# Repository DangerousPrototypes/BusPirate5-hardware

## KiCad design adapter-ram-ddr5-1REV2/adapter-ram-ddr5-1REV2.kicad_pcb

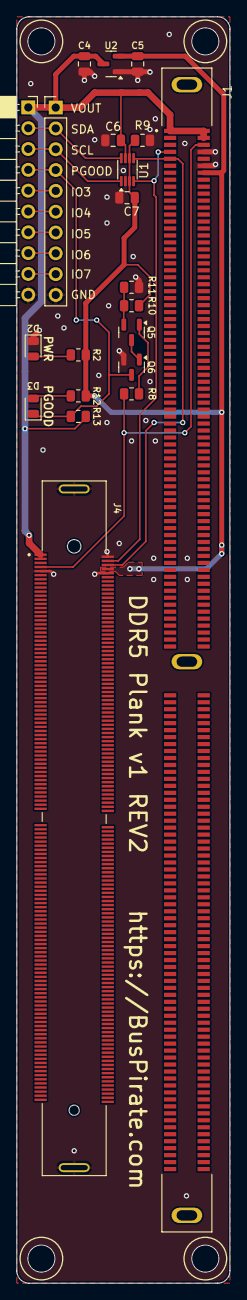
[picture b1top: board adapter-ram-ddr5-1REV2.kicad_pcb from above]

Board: 2 copper layers, 26.0 x 154.5 mm, 21 parts (0 on the bottom side), 19 nets.

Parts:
C4, C5, C6, C7: 10uF/6.3V; C_0805_2012Metric
D2, D3: LED; LED_0805_2012Metric
J1: DDR504111002KQ; DDR5 UDIMM GENERIC
J2: Conn_01x10; PinSocket_1x10_P2.54mm_Horizontal
J3: Conn_01x10; PinHeader_1x10_P2.54mm_Vertical
J4: 10160554-001SHLF; AMPHENOL_10160554-001SHLF
Q5: BC807; SOT-23
Q6: BC817; SOT-23
R2, R12, R13: 6.8K; R_0805_2012Metric
R8, R9: 1K; R_0805_2012Metric
R10: 680R; R_0805_2012Metric
R11: 330R; R_0805_2012Metric
U1: TXS0102DCU; VSSOP-8_2.3x2mm_P0.5mm
U2: ME6206A33XG; SOT-23

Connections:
+3.3V: C5.1, C7.1, J1.151, J4.8, R2.1, R9.2, R10.2, R12.1, U1.3 (VCCA), U1.6 (OE), U2.2 (VO)
BULK_VIN: C4.1, C6.2, J1.01, J1.145, J1.146, J2.1, J3.1, J4.1, J4.3, R13.2, U1.7 (VCCB), U2.3 (VI)
GND: C4.2, C5.2, C6.1, C7.2, D2.1 (K), J1.148, J1.150, J2.10, J3.10, J4.2, J4.9, J4.10, J4.SH, Q6.2 (E), R9.1, R11.1, U1.2 (GND), U2.1 (GND)
HSCL: J1.04, J4.4, U1.4 (A2)
HSDA: J1.05, J4.6, U1.5 (A1)
unnamed: D2.2 (A), R2.2
unnamed: D3.2 (A), R12.2
unnamed: J2.5, J3.5
unnamed: J2.6, J3.6
unnamed: J2.7, J3.7
unnamed: J2.8, J3.8
unnamed: J2.9, J3.9
unnamed: Q5.1 (B), R8.2
unnamed: Q5.3 (C), Q6.1 (B)
unnamed: Q5.2 (E), R10.1, R11.2
PWR_GOOD: J1.147, J4.7, R8.1
PWR_GOOD_OUT: D3.1 (K), J2.4, J3.4, Q6.3 (C), R13.1
SCL: J2.3, J3.3, U1.1 (B2)
SDA: J2.2, J3.2, U1.8 (B1)

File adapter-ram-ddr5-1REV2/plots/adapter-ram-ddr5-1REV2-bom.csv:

"Reference","Value","Footprint","Qty","szlcsc_partnum","DNP"
"C4,C5,C6,C7","10uF/6.3V","Capacitor_SMD:C_0805_2012Metric","4","C307525",""
"D2,D3","LED","LED_SMD:LED_0805_2012Metric","2","",""
"J1","DDR504111002KQ","footprints:DDR5 UDIMM GENERIC","1","",""
"J2","Conn_01x10","Connector_PinSocket_2.54mm:PinSocket_1x10_P2.54mm_Horizontal","1","",""
"J4","10160554-001SHLF","footprints:AMPHENOL_10160554-001SHLF","1","",""
"Q5","BC807","Package_TO_SOT_SMD:SOT-23","1","C21714130",""
"Q6","BC817","Package_TO_SOT_SMD:SOT-23","1","C39828",""
"R2,R12,R13","6.8K","Resistor_SMD:R_0805_2012Metric","3","C17772",""
"R8,R9","1K","Resistor_SMD:R_0805_2012Metric","2","C17513",""
"R10","680R","Resistor_SMD:R_0805_2012Metric","1","C17798",""
"R11","330R","Resistor_SMD:R_0805_2012Metric","1","C17630",""
"U1","TXS0102DCU","Package_SO:VSSOP-8_2.3x2mm_P0.5mm","1","C53434",""
"U2","ME6206A33XG","Package_TO_SOT_SMD:SOT-23","1","C161345",""

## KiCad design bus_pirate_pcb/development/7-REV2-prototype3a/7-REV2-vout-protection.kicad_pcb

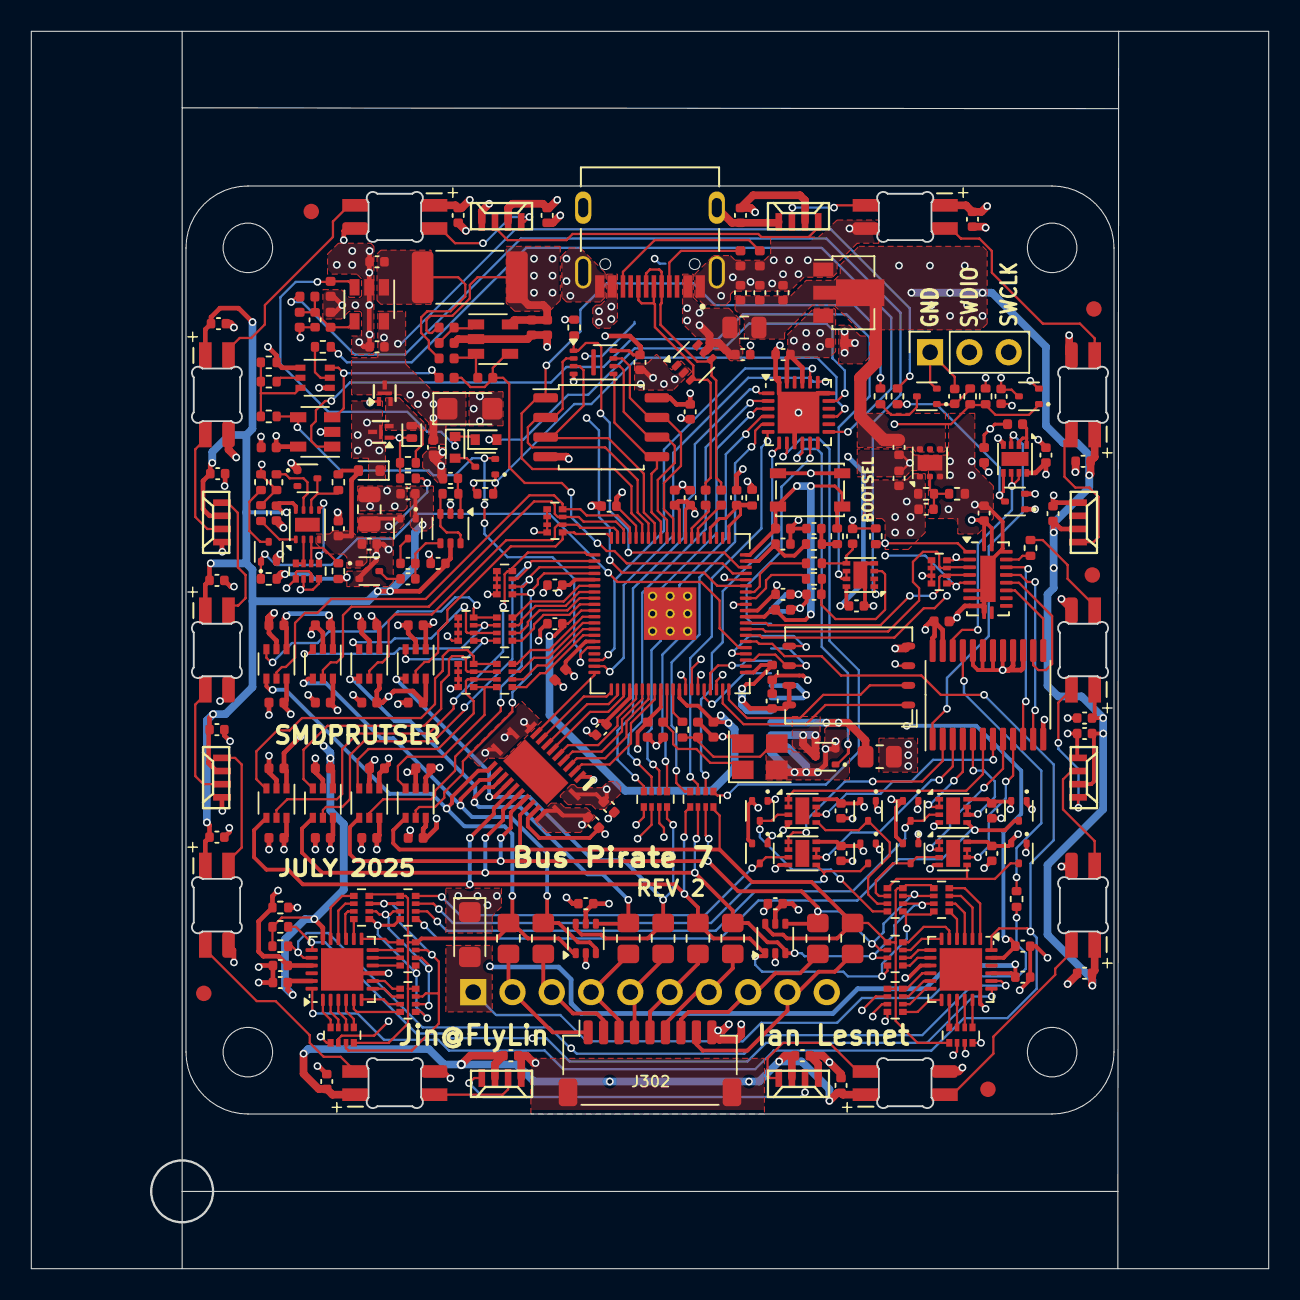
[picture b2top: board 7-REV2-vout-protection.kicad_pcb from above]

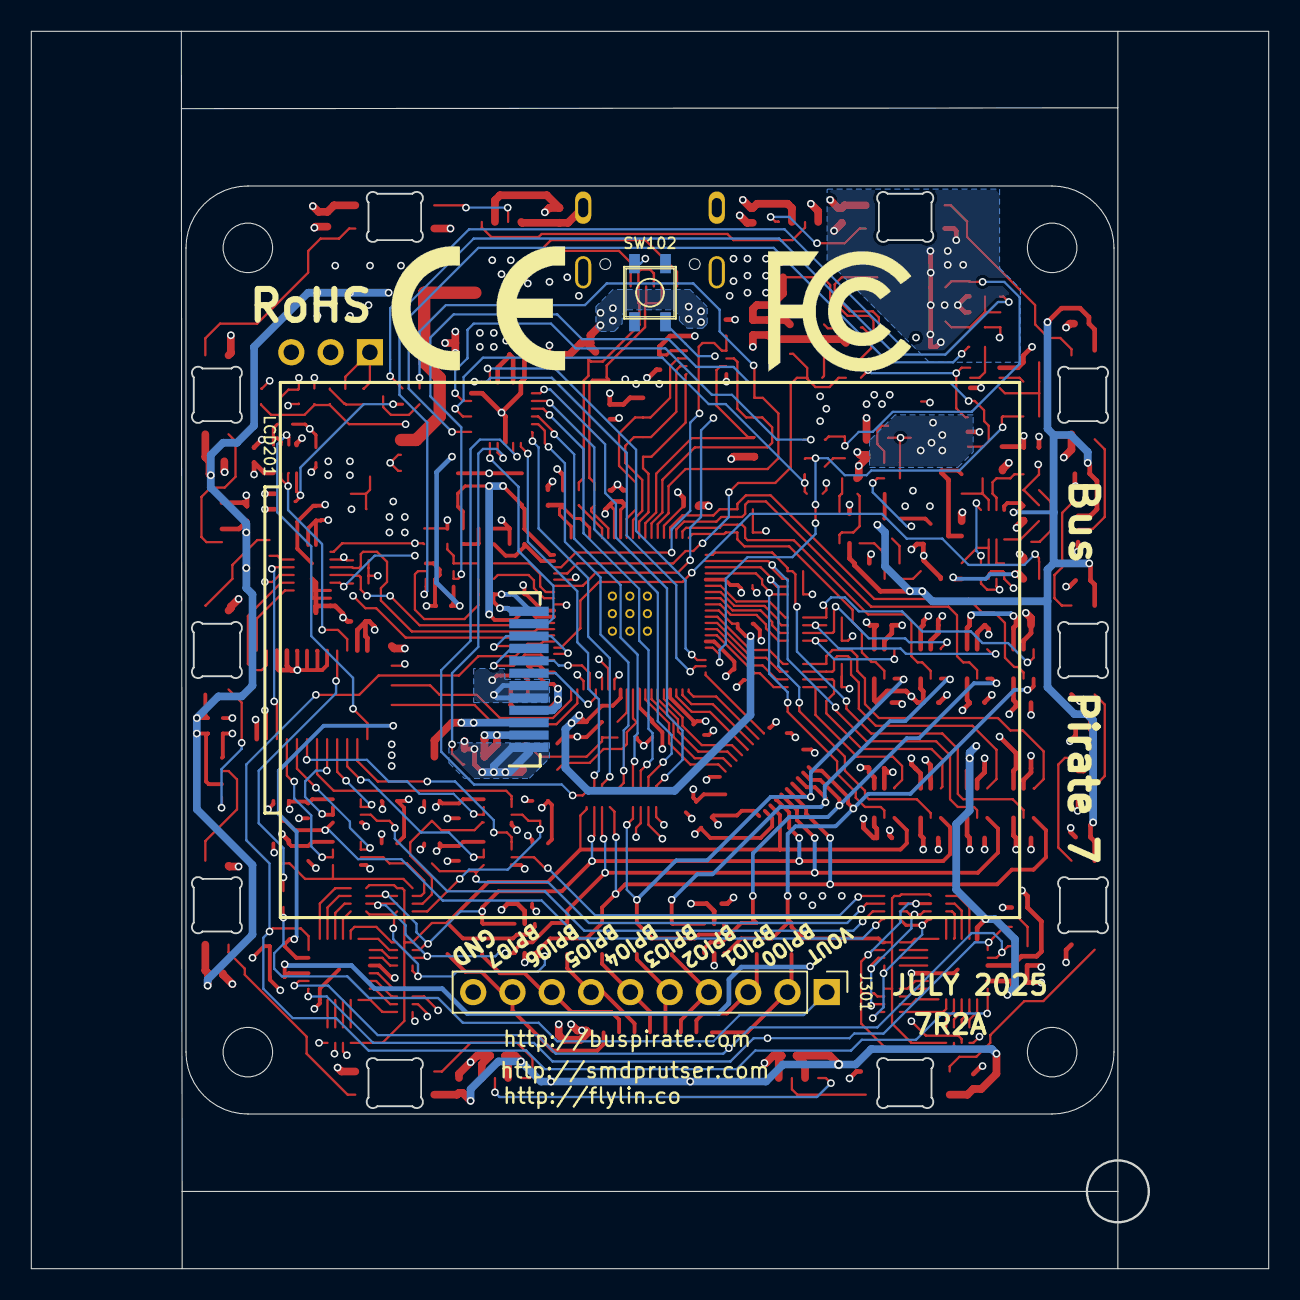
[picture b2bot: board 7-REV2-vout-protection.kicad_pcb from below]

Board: 4 copper layers, 80.0 x 80.0 mm, 276 parts (5 on the bottom side), 223 nets.

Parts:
C1, C2, C3, C5, C7, C8, C9, C14, C15, C16, C17, C20, C22, C28, C32, C110, C111, C112, C113, C114, C115, C116, C117, C118, C301, C302, C303, C304, C305, C306, C307, C308, C309, C310, C311, C312, C313, C314, C315, C316, C403, C415, C416, C503, C507, C508, C509, C510, C602, C605, C701, C702, C703, C704, C705, C706, C707, C708, C710, C712, C713, C714, C715, C716, C717, C718, C719, C720: 0.1uF; C_0402_1005Metric
C4, C6, C10, C11, C18, C19, C23, C24, C29, C36, C104, C109, C201, C202, C401, C402, C404, C407, C413, C601: 10uF/6.3V; C_0402_1005Metric
C12, C26, C408: 120pF; C_0402_1005Metric
C25, C27, C30, C31, C33, C35: 10uF/6.3v; C_0402_1005Metric
C34: 10uF/16v; C_0805_2012Metric
C105, C106: 15pF; C_0402_1005Metric
D1, D2, D3, D4, D5, D6, D7, D8, D9, D14, D15, D16: BAS40-04; SOT-523
D11: SMF24CA; D_SMF
D12: SMF5.0A; D_SMF
D13: PESD12VV1BL; D_SOD-882D
D18, D602, D603: 1N4148WT; D_SOD-523
FID1, FID2, FID3, FID4, FID5: Fiducial; Fiducial_1mm_Mask2mm
H1, H2, H3, H4: MountingHole; MountingHole_3.2mm_M3
J201: Conn_01x03; PinSocket_1x03_P2.54mm_Vertical
J202: TYPE-C-31-M-12; HRO_TYPE-C-31-M-12
J301: Conn_01x10; PinHeader_1x10_P2.54mm_Vertical
J302: Conn_01x09; JST_SH_SM09B-SRSS-TB_1x09-1MP_P1.00mm_Horizontal
L201: CBW201209U300T; L_0805_2012Metric
LCD201: TFT_20_QT200H1201
LED701, LED704, LED707, LED708, LED712, LED716, LED717, LED720: SK6812-side-a_b
LED702, LED703, LED705, LED706, LED710, LED713, LED714, LED715, LED718, LED719: SK6812-mini-e; SK6812-MINI-E
Q1, Q2, Q5, Q6: 2N7002KT; SOT-523
Q3, Q4: PMXB56EN; DFN1010D-3_SOT1215_NEX
Q601: MMDT3906DW; SOT-363_SC-70-6
Q602: BC2301T 2.8A; SOT-523
R1: 10R; R_0402_1005Metric
R2, R12, R502, R602, R603: 1k; R_0402_1005Metric
R3: 110k; R_0402_1005Metric
R4, R5, R42, R319, R401: 100k; R_0402_1005Metric
R6, R8, R9, R11, R40, R301, R406, R407, R414, R415, R606, R609, R610, R611, R613: 10k; R_0402_1005Metric
R10: 470k; R_0402_1005Metric
R13, R14, R15, R16, R17, R18, R19, R20: 120R 0.5W; R_0805_2012Metric_Pad1.20x1.40mm_HandSolder
R21, R103, R202, R203: 27R; R_0402_1005Metric
R22: 100R; R_0402_1005Metric
R23: 3.3k; R_0402_1005Metric
R33, R37: 18k; R_0402_1005Metric
R39: 180k; R_0402_1005Metric
R41, R43, R201, R204: 5.1k; R_0402_1005Metric
R209: 33R; R_0805_2012Metric
R320: 0R; R_0402_1005Metric
R403: 102k; R_0402_1005Metric
R404: 133k; R_0402_1005Metric
R405, R604, R605: 33k; R_0402_1005Metric
R601: 0R2; R_2512_6332Metric_Pad1.40x3.35mm_HandSolder
R608: 200R; R_0402_1005Metric
RN1, RN2, RN8, RN12, RN303, RN308, RN317, RN318: 100k; R_Array_Convex_4x0402
RN3, RN9: 10k; R_Array_Convex_4x0402
RN4, RN7, RN302, RN307: 4.7k; R_Array_Convex_4x0402
RN5, RN6: 2.2k; R_Array_Convex_4x0402
RN10, RN11: 1M; R_Array_Convex_4x0402
RN301, RN306: 120R; R_Array_Convex_4x0402
SW101: TS3425BA 098 2.5H 250gf; SW_SPST_PTS810
SW102: TS3315A 250gf 025; GT-TC026X-HXXX-LX
U1: RP2350B; qfn80
U2: AiP74LVC8T245QE24.TR; NXP-DHVQFN24
U4: XL9555QF24; QFN-24-1EP_4x4mm_P0.5mm_EP2.7x2.7mm
U5, U9, U10, U11, U12, U13: GS358-FR; DFN-8-1EP_2x2mm_P0.5mm_EP1.05x1.75mm
U6, U7: TCA6416ARTWR; QFN-24-1EP_4x4mm_P0.5mm_EP2.75x2.75mm
U8: APS6404L-3SQR-ZR; USON-8-3x2mm_P0.5mm_EPthin
U14, U15, U16: SP3002-04JTG; SOT-363_SC-70-6
U17: TLV75801PDRV; WSON-6-1EP_2x2mm_P0.65mm_EP1x1.6mm
U18: 74LVC2G14; SOT-363_SC-70-6
U102: W25Q128JVSIQ; SOP-8_5.28x5.23mm_P1.27mm
U105: MT29F2G01ABAGDWB-IT:G; U-PDFN-8
U117: LM393BIDSGR; WSON-8-1EP_2x2mm_P0.5mm_EP0.9x1.6mm
U301, U302, U303, U304, U305, U306, U307, U308: AiP74LVC1T45GC363.TR; SOT-363_SC-70-6
U401: ME6211A33PG-N; SOT-89-3
U402: CD4067; TSSOP-24_4.4x7.8mm_P0.65mm
U403: AP2127K-ADJ; SOT-23-5
U503: 74HCT245BQ; DHVQFN-20-1EP_2.5x4.5mm_P0.5mm_EP1x3mm
U601: GS321A-TR; SOT-23-5
U602: GSV331-TR; SOT-23-5
Y101: ABM8-272-T3; Crystal_SMD_3225-4Pin_3.2x2.5mm
logo1: fcc_logo; logo_fcc
logo2: ce_logo; CE-Logo_11.2x8mm_SilkScreen

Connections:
+1V1: C2.1, C11.1, C12.1, C117.1, C118.1, R3.1, U1.10 (DVDD), U1.32 (DVDD), U1.51 (DVDD), U17.1 (OUT)
+3V3: C1.1, C3.2, C5.2, C7.1, C8.1, C15.2, C17.2, C18.1, C19.1, C104.1, C110.1, C111.1, C112.1, C113.1, C114.1, C115.1, C116.1, C301.2, C302.2, C303.2, C307.2, C308.2, C309.2, C313.2, C314.2, C402.1, C413.1, C605.1, LCD201.4 (VCC), Q601.1 (E1), Q601.4 (E2), R1.1, R6.1, R8.1, R9.1, R21.2, R37.1, R43.1, R609.1, R613.1, SW101.1 (A), U1.5 (IOVDD), U1.15 (IOVDD), U1.24 (IOVDD), U1.29 (IOVDD), U1.41 (IOVDD), U1.50 (IOVDD), U1.60 (IOVDD), U1.68 (USB_OTP_VDD), U1.69 (QSPI_IOVDD), U1.76 (IOVDD), U2.1 (VCCA), U4.21 (VCC), U4.23 (ADDR1), U5.8 (V+), U6.23 (VCCI), U7.18 (ADDR), U7.23 (VCCI), U8.8 (VCC), U102.8 (VCC), U105.3 (WP/IO2), U105.7 (HOLD/IO3), U105.8 (VCC), U301.1 (VCCA), U302.1 (VCCA), U303.1 (VCCA), U304.1 (VCCA), U305.1 (VCCA), U306.1 (VCCA), U307.1 (VCCA), U308.1 (VCCA), U401.3 (VOUT), U602.5 (V+)
+9V: C34.1, D14.2, R33.1
+VUSB: C10.1, C20.2, C23.1, C27.1, C29.1, C30.1, C31.2, C201.2, C202.2, C401.1, C403.2, C503.2, C507.2, C508.2, C509.2, C510.2, C601.1, C602.2, C701.2, C702.2, C703.2, C704.2, C705.2, C706.2, C707.2, C708.2, C710.2, C712.2, C713.2, C714.2, C715.2, C716.2, C717.2, C718.2, C719.2, C720.2, D1.2, D2.2, D3.2, D4.2, D5.2, D6.2, D7.2, D8.2, D9.2, D14.1, L201.1, LED701.3 (VDD), LED702.1 (VDD), LED703.1 (VDD), LED704.3 (VDD), LED705.1 (VDD), LED706.1 (VDD), LED707.3 (VDD), LED708.3 (VDD), LED710.1 (VDD), LED712.3 (VDD), LED713.1 (VDD), LED714.1 (VDD), LED715.1 (VDD), LED716.3 (VDD), LED717.3 (VDD), LED718.1 (VDD), LED719.1 (VDD), LED720.3 (VDD), R209.1, R601.1, R602.2, U9.8 (V+), U10.8 (V+), U11.8 (V+), U12.8 (V+), U13.8 (V+), U14.5 (VP), U15.5 (VP), U17.4 (EN), U17.6 (IN), U18.5 (VCC), U117.8 (V+), U401.2 (VIN), U402.23 (I8), U402.24 (VCC), U503.1 (A->B), U503.20 (VCC), U601.5 (V+)
+VUSB_RAW: C24.1, J202.A4B9 (VBUS), J202.B4A9 (VBUS), L201.2, U16.5 (VP)
-5V: C33.1, C35.2, D16.1, D18.2 (A), R40.2, U117.4 (V-)
AMUX_OUT: R406.2, R407.2, U1.56 (GPIO45_ADC5)
AMUX_S0: U402.10 (S0), U503.17 (B1)
AMUX_S0_3V3: RN1.8 (R1.8), U1.47 (GPIO38), U503.3 (A1)
AMUX_S1: U402.11 (S1), U503.16 (B2)
AMUX_S1_3V3: RN1.7 (R1.8), U1.48 (GPIO39), U503.4 (A2)
AMUX_S2: U402.14 (S2), U503.15 (B3)
AMUX_S2_3V3: RN1.6 (R1.8), U1.49 (GPIO40_ADC0), U503.5 (A3)
AMUX_S3: U402.13 (S3), U503.14 (B4)
AMUX_S3_3V3: RN1.5 (R1.8), U1.52 (GPIO41_ADC1), U503.6 (A4)
BPIO0_TVS: R13.1, RN6.4 (R1.1), RN7.4 (R1.1), RN8.8 (R1.8), RN9.8 (R1.8), RN10.1 (R1.1), RN318.5 (R1.8), U2.14 (B8), U14.1 (I/O_1), U301.4 (B)
BPIO1_TVS: R14.1, RN6.3 (R1.1), RN7.3 (R1.1), RN8.7 (R1.8), RN9.7 (R1.8), RN10.2 (R1.1), RN318.6 (R1.8), U2.15 (B7), U14.3 (I/O_2), U302.4 (B)
BPIO2_TVS: R15.1, RN6.2 (R1.1), RN7.2 (R1.1), RN8.6 (R1.8), RN9.6 (R1.8), RN10.3 (R1.1), RN318.7 (R1.8), U2.16 (B6), U14.4 (I/O_3), U303.4 (B)
BPIO3_TVS: R16.1, RN6.1 (R1.1), RN7.1 (R1.1), RN8.5 (R1.8), RN9.5 (R1.8), RN10.4 (R1.1), RN318.8 (R1.8), U2.17 (B5), U14.6 (I/O_4), U304.4 (B)
BPIO4_TVS: R17.1, RN2.8 (R1.8), RN3.8 (R1.8), RN4.4 (R1.1), RN5.4 (R1.1), RN11.1 (R1.1), RN317.5 (R1.8), U2.18 (B4), U15.1 (I/O_1), U305.4 (B)
BPIO5_TVS: R18.1, RN2.7 (R1.8), RN3.7 (R1.8), RN4.3 (R1.1), RN5.3 (R1.1), RN11.2 (R1.1), RN317.6 (R1.8), U2.19 (B3), U15.3 (I/O_2), U306.4 (B)
BPIO6_TVS: R19.1, RN2.6 (R1.8), RN3.6 (R1.8), RN4.2 (R1.1), RN5.2 (R1.1), RN11.3 (R1.1), RN317.7 (R1.8), U2.20 (B2), U15.4 (I/O_3), U307.4 (B)
BPIO7_TVS: R20.1, RN2.5 (R1.8), RN3.5 (R1.8), RN4.1 (R1.1), RN5.1 (R1.1), RN11.4 (R1.1), RN317.8 (R1.8), U2.21 (B1), U15.6 (I/O_4), U308.4 (B)
BUFDIR0: RN303.8 (R1.8), U1.77 (GPIO0), U301.5 (DIR)
BUFDIR1: RN303.7 (R1.8), U1.78 (GPIO1), U302.5 (DIR)
BUFDIR2: RN303.6 (R1.8), U1.79 (GPIO2), U303.5 (DIR)
BUFDIR3: RN303.5 (R1.8), U1.80 (GPIO3), U304.5 (DIR)
BUFDIR4: RN308.8 (R1.8), U1.1 (GPIO4), U305.5 (DIR)
BUFDIR5: RN308.7 (R1.8), U1.2 (GPIO5), U306.5 (DIR)
BUFDIR6: RN308.6 (R1.8), U1.3 (GPIO6), U307.5 (DIR)
BUFDIR7: RN308.5 (R1.8), U1.4 (GPIO7), U308.5 (DIR)
BUFIO0: RN301.8 (R1.8), U1.6 (GPIO8)
BUFIO1: RN301.7 (R1.8), U1.7 (GPIO9)
BUFIO2: RN301.6 (R1.8), U1.8 (GPIO10)
BUFIO3: RN301.5 (R1.8), U1.9 (GPIO11)
BUFIO4: RN306.8 (R1.8), U1.11 (GPIO12)
BUFIO5: RN306.7 (R1.8), U1.12 (GPIO13)
BUFIO6: RN306.6 (R1.8), U1.13 (GPIO14)
BUFIO7: RN306.5 (R1.8), U1.14 (GPIO15)
BUTTONS: SW102.3, U1.55 (GPIO44_ADC4)
CURRENT_ADJ: U5.6 (-), U5.7, U602.1 (+)
CURRENT_ADJ_MCU: R415.2, U1.54 (GPIO43_ADC3)
CURRENT_DETECT: Q602.2 (S), R610.2, U1.16 (GPIO16), U602.4
CURRENT_EN: Q602.1 (G), R613.2, U4.15
CURRENT_EN_OVERRIDE: D603.2 (A), U4.17
CURRENT_RESET: R611.1, U4.13
CURRENT_SENSE: R605.1, R606.2, U1.57 (GPIO46_ADC6), U601.4
DISPLAY_BACKLIGHT: Q2.1 (G), U4.10
DISPLAY_CS: LCD201.8 (CS), U1.37 (GPIO29)
DISPLAY_DP: LCD201.7 (WR/SPI_A0), U1.36 (GPIO28)
DISPLAY_RESET: LCD201.11 (RESET), U4.11
FLASH_CS: U1.39 (GPIO31), U105.1 (CS)
GND: C1.2, C2.2, C3.1, C4.2, C5.1, C6.2, C7.2, C8.2, C9.2, C10.2, C11.2, C14.1, C15.1, C16.1, C17.1, C18.2, C19.2, C20.1, C22.2, C23.2, C24.2, C25.1, C26.2, C27.2, C29.2, C30.2, C31.1, C33.2, C34.2, C35.1, C36.2, C104.2, C105.2, C106.2, C109.2, C110.2, C111.2, C112.2, C113.2, C114.2, C115.2, C116.2, C117.2, C118.2, C201.1, C202.1, C301.1, C302.1, C303.1, C304.2, C305.2, C306.2, C307.1, C308.1, C309.1, C310.2, C311.2, C312.2, C313.1, C314.1, C315.2, C316.2, C401.2, C402.2, C403.1, C404.2, C407.2, C413.2, C415.1, C416.1, C503.1, C507.1, C508.1, C509.1, C510.1, C601.2, C602.1, C605.2, C701.1, C702.1, C703.1, C704.1, C705.1, C706.1, C707.1, C708.1, C710.1, C712.1, C713.1, C714.1, C715.1, C716.1, C717.1, C718.1, C719.1, C720.1, D1.1, D2.1, D3.1, D4.1, D5.1, D6.1, D7.1, D8.1, D9.1, D11.1 (A1), D12.2 (A2), D15.1, D16.2, J201.1, J202.A1B12 (GND), J202.B1A12 (GND), J202.S1 (SHIELD), J202.S2 (SHIELD), J202.S3 (SHIELD), J202.S4 (SHIELD), J301.10, J302.9, LCD201.1 (GND), LCD201.5 (GND), LCD201.6 (GND), LCD201.12 (GND), LED701.1 (VSS), LED702.3 (VSS), LED703.3 (VSS), LED704.1 (VSS), LED705.3 (VSS), LED706.3 (VSS), LED707.1 (VSS), LED708.1 (VSS), LED710.3 (VSS), LED712.1 (VSS), LED713.3 (VSS), LED714.3 (VSS), LED715.3 (VSS), LED716.1 (VSS), LED717.1 (VSS), LED718.3 (VSS), LED719.3 (VSS), LED720.1 (VSS), Q1.2 (S), Q2.2 (S), Q5.2 (S), Q6.2 (S), R4.1, R5.2, R11.2, R201.1, R204.1, R301.2, R401.2, R405.2, R407.1, R604.1, RN1.1 (R1.1), RN1.2 (R1.1), RN1.3 (R1.1), RN1.4 (R1.1), RN12.1 (R1.1), RN12.3 (R1.1), RN302.1 (R1.1), RN302.2 (R1.1), RN302.3 (R1.1), RN302.4 (R1.1), RN303.1 (R1.1), RN303.2 (R1.1), RN303.3 (R1.1), RN303.4 (R1.1), RN307.1 (R1.1), RN307.2 (R1.1), RN307.3 (R1.1), RN307.4 (R1.1), RN308.1 (R1.1), RN308.2 (R1.1), RN308.3 (R1.1), RN308.4 (R1.1), SW102.2, U1.81 (GND), U2.2 (DIR), U2.11 (GND), U2.12 (GND), U2.13 (GND), U2.22 (~OE), U4.9 (GND), U4.18 (ADDR0), U4.24 (ADDR2), U4.25 (EP), U5.4 (V-), U5.9 (PAD), U6.9 (GND), U6.18 (ADDR), U6.25 (EP), U7.9 (GND), U7.25 (EP), U8.4 (VSS), U9.4 (V-), U10.4 (V-), U11.4 (V-), U12.4 (V-), U13.4 (V-), U14.2 (GND), U15.2 (GND), U16.2 (GND), U17.3 (GND), U17.7 (GND), U18.2 (GND), U102.4 (VSS), U105.4 (VSS), U301.2 (GND), U302.2 (GND), U303.2 (GND), U304.2 (GND), U305.2 (GND), U306.2 (GND), U307.2 (GND), U308.2 (GND), U401.1 (GND), U402.12 (GND), U402.15 (~E), U402.16 (I15), U402.17 (I14), U402.18 (I13), U402.19 (I12), U402.20 (I11), U403.2 (GND), U503.7 (A5), U503.8 (A6), U503.9 (A7), U503.10 (GND), U503.19 (CE), U503.21 (EP), U601.2 (V-), U602.2 (V-), Y101.2, Y101.4
I2C_RESET: U1.46 (GPIO37), U6.24 (~RESET), U7.24 (~RESET)
I2C_SCL: R9.2, U1.19 (GPIO19), U4.19 (SCL), U6.19 (SCL), U7.19 (SCL)
I2C_SDA: R8.2, U1.18 (GPIO18), U4.20 (SDA), U6.20 (SDA), U7.20 (SDA)
LA_BPIO0_TVS: U1.20 (GPIO20), U2.10 (A8)
LA_BPIO1_TVS: U1.21 (GPIO21), U2.9 (A7)
LA_BPIO2_TVS: U1.22 (GPIO22), U2.8 (A6)
LA_BPIO3_TVS: U1.23 (GPIO23), U2.7 (A5)
LA_BPIO4_TVS: U1.25 (GPIO24), U2.6 (A4)
LA_BPIO5_TVS: U1.26 (GPIO25), U2.5 (A3)
LA_BPIO6_TVS: U1.27 (GPIO26), U2.4 (A2)
LA_BPIO7_TVS: U1.28 (GPIO27), U2.3 (A1)
LEDS_CDO: R502.1, U503.18 (B0)
MCU_BOOTLOAD: R12.2, U1.75 (QSPI_SS), U102.1 (CS)
MCU_RESET: C22.1, Q5.3 (D), U1.35 (RUN)
MUX_BPIO0_TVS: U9.1, U9.2 (-), U402.2 (I7)
MUX_BPIO1_TVS: U9.6 (-), U9.7, U402.3 (I6)
MUX_BPIO2_TVS: U10.1, U10.2 (-), U402.4 (I5)
MUX_BPIO3_TVS: U10.6 (-), U10.7, U402.5 (I4)
MUX_BPIO4_TVS: U11.1, U11.2 (-), U402.6 (I3)
MUX_BPIO5_TVS: U11.6 (-), U11.7, U402.7 (I2)
MUX_BPIO6_TVS: U12.1, U12.2 (-), U402.8 (I1)
MUX_BPIO7_TVS: U12.6 (-), U12.7, U402.9 (I0)
MUX_VREF_VOUT: U13.6 (-), U13.7, U402.22 (I9)
unnamed: C6.1, R21.1, R103.2
unnamed: C26.1, R39.1, U18.1
unnamed: C28.1, C32.1, U18.4
unnamed: C28.2, D14.3
unnamed: C32.2, D16.3
unnamed: C106.1, R2.1, Y101.3
unnamed: D13.1 (A1), Q3.1 (G), Q4.1 (G), R22.1, R23.1, R33.2, R41.1, R42.2
unnamed: D13.2 (A2), Q3.2 (S), Q4.2 (S), R42.1
unnamed: D602.2 (A), Q602.3 (D)
unnamed: J202.A5 (CC1), R201.2
unnamed: J202.B5 (CC2), R204.2
unnamed: J301.2, J302.1, R13.2
unnamed: J301.3, J302.2, R14.2
unnamed: J301.4, J302.3, R15.2
unnamed: J301.5, J302.4, R16.2
unnamed: J301.6, J302.5, R17.2
unnamed: J301.7, J302.6, R18.2
unnamed: J301.8, J302.7, R19.2
unnamed: J301.9, J302.8, R20.2
unnamed: LCD201.3 (LED-A), R209.2
unnamed: LCD201.2 (LED-K), Q2.3 (D)
unnamed: LED701.4 (DI), LED702.2 (DO)
unnamed: LED701.2 (DO), LED704.4 (DI)
unnamed: LED702.4 (DI), LED706.2 (DO)
unnamed: LED703.4 (DI), LED704.2 (DO)
unnamed: LED703.2 (DO), LED705.4 (DI)
unnamed: LED705.2 (DO), LED720.4 (DI)
unnamed: LED706.4 (DI), LED708.2 (DO)
unnamed: LED707.4 (DI), LED719.2 (DO)
unnamed: LED707.2 (DO), LED713.4 (DI)
unnamed: LED708.4 (DI), LED710.2 (DO)
unnamed: LED710.4 (DI), LED712.2 (DO)
unnamed: LED712.4 (DI), LED714.2 (DO)
unnamed: LED713.2 (DO), LED715.4 (DI)
unnamed: LED714.4 (DI), LED718.2 (DO)
unnamed: LED715.2 (DO), LED716.4 (DI)
unnamed: LED716.2 (DO), LED717.4 (DI)
unnamed: LED717.2 (DO), LED718.4 (DI)
unnamed: LED719.4 (DI), R502.2
unnamed: Q1.3 (D), R12.1
unnamed: C36.1, Q1.1 (G), R10.2
unnamed: Q5.1 (G), R10.1, R11.1, SW101.2 (B)
unnamed: Q6.3 (D), R23.2
unnamed: Q601.2 (B1), R611.2
unnamed: Q601.6 (C1), R608.2, R609.2, R610.1
unnamed: Q601.5 (B2), R608.1
unnamed: Q601.3 (C2), R606.1, U602.3 (-)
unnamed: R22.2, U117.7
unnamed: R39.2, U18.3, U18.6
unnamed: R41.2, U117.1
unnamed: RN2.1 (R1.1), U6.13
unnamed: RN2.2 (R1.1), U6.12
unnamed: RN2.3 (R1.1), U6.11
unnamed: RN2.4 (R1.1), U6.10
unnamed: RN3.1 (R1.1), U6.17
unnamed: RN3.2 (R1.1), U6.16
unnamed: RN3.3 (R1.1), U6.15
unnamed: RN3.4 (R1.1), U6.14
unnamed: RN4.8 (R1.8), U6.5 (P04)
unnamed: RN4.7 (R1.8), U6.6 (P05)
unnamed: RN4.6 (R1.8), U6.7 (P06)
unnamed: RN4.5 (R1.8), U6.8 (P07)
unnamed: RN5.8 (R1.8), U6.1 (P00)
unnamed: RN5.7 (R1.8), U6.2 (P01)
unnamed: RN5.6 (R1.8), U6.3 (P02)
unnamed: RN5.5 (R1.8), U6.4 (P03)
unnamed: RN6.8 (R1.8), U7.1 (P00)
unnamed: RN6.7 (R1.8), U7.2 (P01)
unnamed: RN6.6 (R1.8), U7.3 (P02)
unnamed: RN6.5 (R1.8), U7.4 (P03)
unnamed: RN7.8 (R1.8), U7.5 (P04)
unnamed: RN7.7 (R1.8), U7.6 (P05)
unnamed: RN7.6 (R1.8), U7.7 (P06)
unnamed: RN7.5 (R1.8), U7.8 (P07)
unnamed: RN8.1 (R1.1), U7.13
unnamed: RN8.2 (R1.1), U7.12
unnamed: RN8.3 (R1.1), U7.11
unnamed: RN8.4 (R1.1), U7.10
unnamed: RN9.1 (R1.1), U7.17
unnamed: RN9.2 (R1.1), U7.16
unnamed: RN9.3 (R1.1), U7.15
unnamed: RN9.4 (R1.1), U7.14
unnamed: RN10.8 (R1.8), U4.1 (P00)
unnamed: RN10.7 (R1.8), U4.2 (P01)
unnamed: RN10.6 (R1.8), U4.3 (P02)
unnamed: RN10.5 (R1.8), U4.4 (P03)
unnamed: RN11.8 (R1.8), U4.5 (P04)
unnamed: RN11.7 (R1.8), U4.6 (P05)
unnamed: RN11.6 (R1.8), U4.7 (P06)
unnamed: RN11.5 (R1.8), U4.8 (P07)
unnamed: RN12.7 (R1.8), RN12.8 (R1.8), U117.2 (-)
unnamed: R37.2, RN12.6 (R1.8), U117.3 (+)
unnamed: RN12.5 (R1.8), U117.5 (+)
unnamed: RN301.1 (R1.1), RN302.8 (R1.8), U301.3 (A)
unnamed: RN301.2 (R1.1), RN302.7 (R1.8), U302.3 (A)
unnamed: RN301.3 (R1.1), RN302.6 (R1.8), U303.3 (A)
unnamed: RN301.4 (R1.1), RN302.5 (R1.8), U304.3 (A)
unnamed: RN306.1 (R1.1), RN307.8 (R1.8), U305.3 (A)
unnamed: RN306.2 (R1.1), RN307.7 (R1.8), U306.3 (A)
unnamed: RN306.3 (R1.1), RN307.6 (R1.8), U307.3 (A)
unnamed: RN306.4 (R1.1), RN307.5 (R1.8), U308.3 (A)
unnamed: D1.3, RN317.1 (R1.1), U12.5 (+)
unnamed: D2.3, RN317.2 (R1.1), U12.3 (+)
unnamed: D4.3, RN317.3 (R1.1), U11.5 (+)
unnamed: D3.3, RN317.4 (R1.1), U11.3 (+)
unnamed: D5.3, RN318.1 (R1.1), U10.5 (+)
unnamed: D6.3, RN318.2 (R1.1), U10.3 (+)
unnamed: D8.3, RN318.3 (R1.1), U9.5 (+)
unnamed: D7.3, RN318.4 (R1.1), U9.3 (+)
unnamed: C109.1, R103.1, U1.59 (ADC_AVDD)
unnamed: C4.1, R1.2, U1.61 (VREG_AVDD), U1.64 (VREG_VIN)
unnamed: C105.1, U1.30 (XIN), Y101.1
unnamed: R2.2, U1.31 (XOUT)
unnamed: C415.2, R414.1, U5.3 (+)
unnamed: C416.2, R415.1, U5.5 (+)
unnamed: U13.3 (+), U402.1 (COM)
unnamed: R406.1, U13.1, U13.2 (-)
unnamed: D9.3, R319.1, U13.5 (+)
unnamed: C12.2, R3.2, R5.1, U17.2 (FB)
unnamed: D15.3, R40.1, U117.6 (-)
unnamed: R320.1, U402.21 (I10)
unnamed: C408.2, R403.2, R404.2, R405.1, U403.4 (ADJ)
unnamed: R602.1, R604.2, U601.1 (+)
unnamed: R603.1, R605.2, U601.3 (-)
QSPI_SCLK: U1.71 (QSPI_SCLK), U8.6 (CLK), U102.6 (CLK)
QSPI_SD0: U1.72 (QSPI_SD0), U8.5 (DI), U102.5 (DI)
QSPI_SD1: U1.74 (QSPI_SD1), U8.2 (DO), U102.2 (DO)
QSPI_SD2: U1.73 (QSPI_SD2), U8.3 (WP), U102.3 (WP)
QSPI_SD3: U1.70 (QSPI_SD3), U8.7 (HOLD), U102.7 (HOLD)
QSPI_SS_2: R6.2, U1.58 (GPIO47_ADC7), U8.1 (CS)
RGB_CDO: R4.2, U1.38 (GPIO30), U503.2 (A0)
SPI_CDI: U1.40 (GPIO32), U105.2 (SO/IO1)
SPI_CDO: LCD201.10 (SPI_SDA), U1.44 (GPIO35), U105.5 (SI/IO0)
SPI_CLK: LCD201.9 (RS/SPI_SCL), U1.43 (GPIO34), U105.6 (SCK)
SWCLK: J201.3, U1.33 (SWCLK)
SWDIO: J201.2, U1.34 (SWD)
USB_D+: R203.1, U1.67 (USB_DP)
USB_D-: R202.1, U1.66 (USB_DM)
USB_N: J202.A7 (DN1), J202.B7 (DN2), R202.2, U16.4 (I/O_3)
USB_P: J202.A6 (DP1), J202.B6 (DP2), R203.2, U16.3 (I/O_2)
VREF_VOUT: C9.1, C14.2, C16.2, C25.2, C304.1, C305.1, C306.1, C310.1, C311.1, C312.1, C315.1, C316.1, C407.1, C408.1, D12.1 (A1), Q3.3 (D), R301.1, R319.2, R404.1, RN12.2 (R1.1), RN12.4 (R1.1), U2.23 (VCCB), U2.24 (VCCB), U6.21 (VCCP), U7.21 (VCCP), U301.6 (VCCB), U302.6 (VCCB), U303.6 (VCCB), U304.6 (VCCB), U305.6 (VCCB), U306.6 (VCCB), U307.6 (VCCB), U308.6 (VCCB), U403.5 (OUT)
VREF_VOUT_PROTECTED: D11.2 (A2), D18.1 (K), J301.1, Q4.3 (D), R320.2
VREG_ADJ: R403.1, U5.1, U5.2 (-)
VREG_ADJ_MCU: R414.2, U1.53 (GPIO42_ADC2)
VREG_EN: D602.1 (K), D603.1 (K), R401.1, U403.3 (SHUTDOWN)
VREG_VIN: C404.1, R601.2, R603.2, U403.1 (VIN)
~Activate_VOUT: Q6.1 (G), R43.2, U1.45 (GPIO36)

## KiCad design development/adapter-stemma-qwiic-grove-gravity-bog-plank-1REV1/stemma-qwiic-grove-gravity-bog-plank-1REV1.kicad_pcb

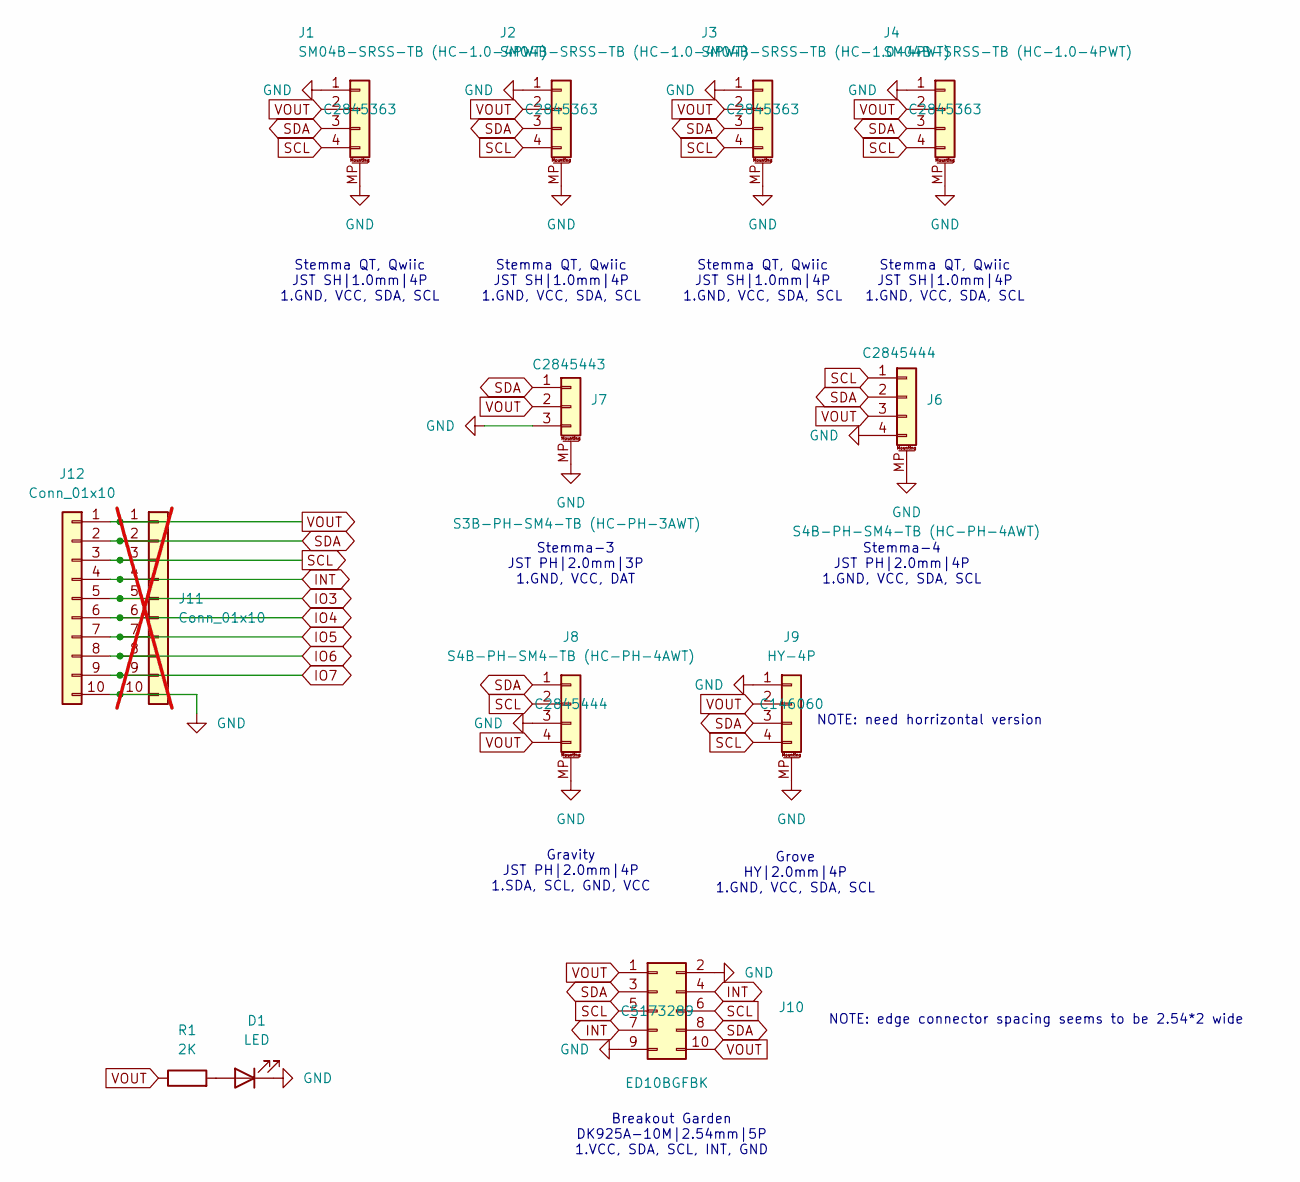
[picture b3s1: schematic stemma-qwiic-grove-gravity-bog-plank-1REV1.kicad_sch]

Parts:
D1: LED; LED_0805_2012Metric
J1, J2, J3, J4: SM04B-SRSS-TB (HC-1.0-4PWT); JST_SH_SM04B-SRSS-TB_1x04-1MP_P1.00mm_Horizontal
J6, J8: S4B-PH-SM4-TB (HC-PH-4AWT); JST_PH_S4B-PH-SM4-TB_1x04-1MP_P2.00mm_Horizontal
J7: S3B-PH-SM4-TB (HC-PH-3AWT); JST_PH_S3B-PH-SM4-TB_1x03-1MP_P2.00mm_Horizontal
J9: HY-4P; CONN-SMD_HY2.0-4P
J10: ED10BGFBK; CONN-TH_SA10BL01D
J11: Conn_01x10; PinHeader_1x10_P2.54mm_Vertical; not fitted
J12: Conn_01x10; PinSocket_1x10_P2.54mm_Horizontal
R1: 2K; R_0805_2012Metric

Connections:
GND: D1.1 (K), J1.1, J1.MP (MountPin), J2.1, J2.MP (MountPin), J3.1, J3.MP (MountPin), J4.1, J4.MP (MountPin), J6.4, J6.MP (MountPin), J7.3, J7.MP (MountPin), J8.3, J8.MP (MountPin), J9.1, J9.MP (MountPin), J10.2, J10.9, J11.10, J12.10
INT: J10.4, J10.7, J11.4, J12.4
IO3: J11.5, J12.5
IO4: J11.6, J12.6
IO5: J11.7, J12.7
IO6: J11.8, J12.8
IO7: J11.9, J12.9
unnamed: D1.2 (A), R1.2
SCL: J1.4, J2.4, J3.4, J4.4, J6.1, J8.2, J9.4, J10.5, J10.6, J11.3, J12.3
SDA: J1.3, J2.3, J3.3, J4.3, J6.2, J7.1, J8.1, J9.3, J10.3, J10.8, J11.2, J12.2
VOUT: J1.2, J2.2, J3.2, J4.2, J6.3, J7.2, J8.4, J9.2, J10.1, J10.10, J11.1, J12.1, R1.1

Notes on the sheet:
Gravity JST PH|2.0mm|4P 1.SDA, SCL, GND, VCC
Stemma QT, Qwiic JST SH|1.0mm|4P 1.GND, VCC, SDA, SCL
Stemma-4 JST PH|2.0mm|4P 1.GND, VCC, SDA, SCL
Stemma-3 JST PH|2.0mm|3P 1.GND, VCC, DAT
NOTE: edge connector spacing seems to be 2.54*2 wide
NOTE: need horrizontal version
Grove HY|2.0mm|4P 1.GND, VCC, SDA, SCL
Breakout Garden DK925A-10M|2.54mm|5P 1.VCC, SDA, SCL, INT, GND

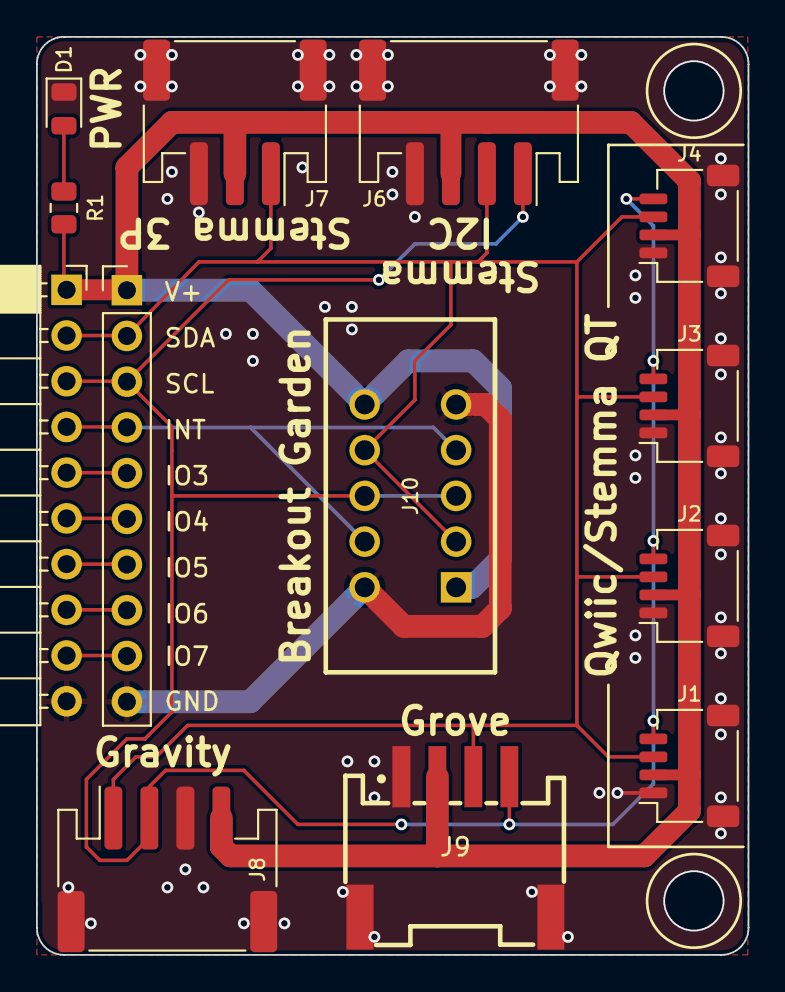
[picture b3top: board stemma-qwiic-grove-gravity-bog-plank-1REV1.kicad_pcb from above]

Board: 2 copper layers, 39.5 x 51.0 mm, 13 parts (0 on the bottom side), 11 nets.

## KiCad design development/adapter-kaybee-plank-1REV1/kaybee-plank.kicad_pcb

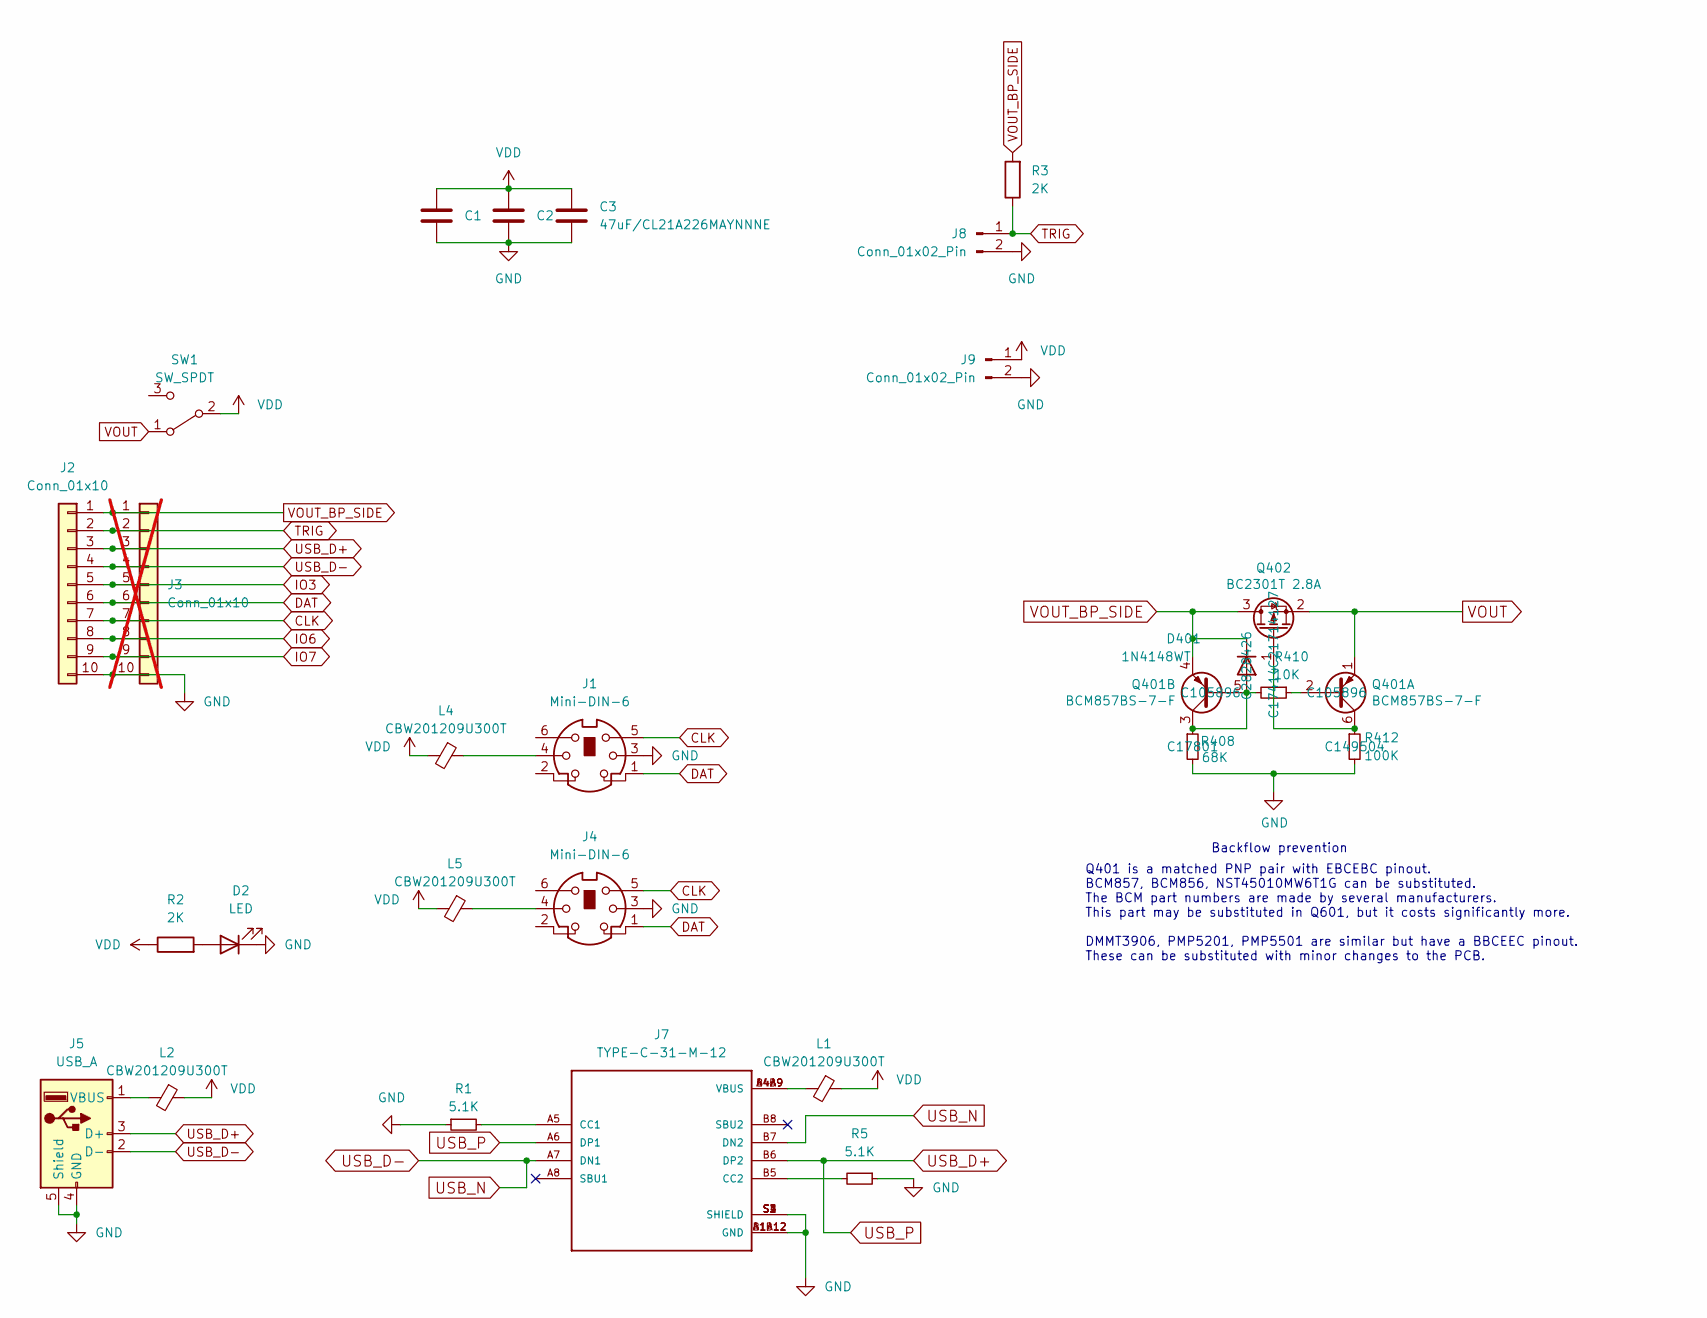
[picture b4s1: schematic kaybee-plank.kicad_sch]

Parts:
C1, C2, C3: 47uF/CL21A226MAYNNNE; C_0805_2012Metric
D2: LED; LED_0805_2012Metric
D401: 1N4148WT; D_SOD-523
J1, J4: Mini-DIN-6; Connector_Mini-DIN_Female_6Pin_2rows
J2: Conn_01x10; PinSocket_1x10_P2.54mm_Horizontal
J3: Conn_01x10; PinHeader_1x10_P2.54mm_Vertical; not fitted
J5: USB_A; USB_A_CONNFLY_DS1095-WNR0
J7: TYPE-C-31-M-12; HRO_TYPE-C-31-M-12
J8, J9: Conn_01x02_Pin; PinHeader_1x02_P2.54mm_Vertical
L1, L2, L4, L5: CBW201209U300T; L_0805_2012Metric
Q401: BCM857BS-7-F; SOT-363_SC-70-6
Q402: BC2301T 2.8A; SOT-523
R1, R5: 5.1K; R_0805_2012Metric
R2, R3: 2K; R_0805_2012Metric
R408: 68K; R_0805_2012Metric
R410: 10K; R_0805_2012Metric
R412: 100K; R_0805_2012Metric
SW1: SW_SPDT; SW_SPDT_PCM12

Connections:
CLK: J1.5, J2.7, J3.7, J4.5
DAT: J1.1, J2.6, J3.6, J4.1
GND: C1.2, C2.2, C3.2, D2.1 (K), J1.3, J2.10, J3.10, J4.3, J5.4 (GND), J5.5 (Shield), J7.A1B12 (GND), J7.B1A12 (GND), J7.S1 (SHIELD), J7.S2 (SHIELD), J7.S3 (SHIELD), J7.S4 (SHIELD), J8.2, J9.2, R1.1, R5.1, R408.2, R412.2
IO3: J2.5, J3.5
IO6: J2.8, J3.8
IO7: J2.9, J3.9
unnamed: D2.2 (A), R2.2
unnamed: D401.2 (A), Q401.3 (C2), Q401.5 (B2), R408.1, R410.2
unnamed: J1.4, L4.1
unnamed: J4.4, L5.1
unnamed: J5.1 (VBUS), L2.2
unnamed: J7.A5 (CC1), R1.2
unnamed: J7.B5 (CC2), R5.2
unnamed: J7.A4B9 (VBUS), J7.B4A9 (VBUS), L1.2
unnamed: Q401.2 (B1), R410.1
unnamed: Q401.6 (C1), Q402.1 (G), R412.1
TRIG: J2.2, J3.2, J8.1, R3.1
USB_D+: J2.3, J3.3, J5.3 (D+), J7.A6 (DP1), J7.B6 (DP2)
USB_D-: J2.4, J3.4, J5.2 (D-), J7.A7 (DN1), J7.B7 (DN2)
VDD: C1.1, C2.1, C3.1, J9.1, L1.1, L2.1, L4.2, L5.2, R2.1, SW1.2 (B)
VOUT: Q401.1 (E1), Q402.2 (S), SW1.1 (A)
VOUT_BP_SIDE: D401.1 (K), J2.1, J3.1, Q401.4 (E2), Q402.3 (D), R3.2

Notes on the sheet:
Q401 is a matched PNP pair with EBCEBC pinout. BCM857, BCM856, NST45010MW6T1G can be substituted. The BCM part numbers are made by several manufacturers. This part may be substituted in Q601, but it costs significantly more. DMMT3906, PMP5201, PMP5501 are similar but have a BBCEEC pinout. These can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
Backflow prevention
